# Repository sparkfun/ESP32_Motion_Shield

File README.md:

SparkFun <PRODUCT NAME>
========================================

The [ESP32 Thing Motion Shield](https://www.sparkfun.com/products/14430) is a versatile addition to our [ESP32 Thing](https://www.sparkfun.com/products/13907).  Small movements can be detected with the tried and true LSM9DS1 IMU, large movements and time can be detected with the addition of a GPS sensor.  There's a port for the [GP-20U7](https://www.sparkfun.com/products/13740) module, and breakout pins for any serial device.  Data can be easily logged by adding an microSD card to the slot.  There is also an additional user led on pin 13.

Repository Contents
-------------------

* **/Documentation** - Test plan and record.
* **/Hardware** - Eagle design files (.brd, .sch)
* **/Production** - Production panel files (.brd)
* **/Software** - Example programs for the ESP32 that can support functions of the Motion Shield.  These are used in the hookup guide.

Documentation
--------------
* **[Motion Shield Hookup Guide](https://learn.sparkfun.com/tutorials/esp32-thing-motion-shield-hookup-guide)** - Basic hookup guide for the ESP32 Motion Shield.
* **[ESP32 Hookup Guide](https://learn.sparkfun.com/tutorials/esp32-thing-hookup-guide)** - Basic hookup guide for the ESP32 Thing.

Product Versions
----------------
* [DEV-14430](https://www.sparkfun.com/products/14430) - ESP32 Motion Shield

Version History
---------------
* [V_1.0.0a](https://github.com/sparkfun/ESP32_Motion_Shield/releases/tag/v1.0.0a) - Software Update.
* [V_1.0.0](https://github.com/sparkfun/ESP32_Motion_Shield/tree/V_1.0.0) - Product release.

License Information
-------------------

This product is _**open source**_! 

Please review the LICENSE.md file for license information. 

If you have any questions or concerns on licensing, please contact techsupport@sparkfun.com.

Distributed as-is; no warranty is given.

- Your friends at SparkFun.

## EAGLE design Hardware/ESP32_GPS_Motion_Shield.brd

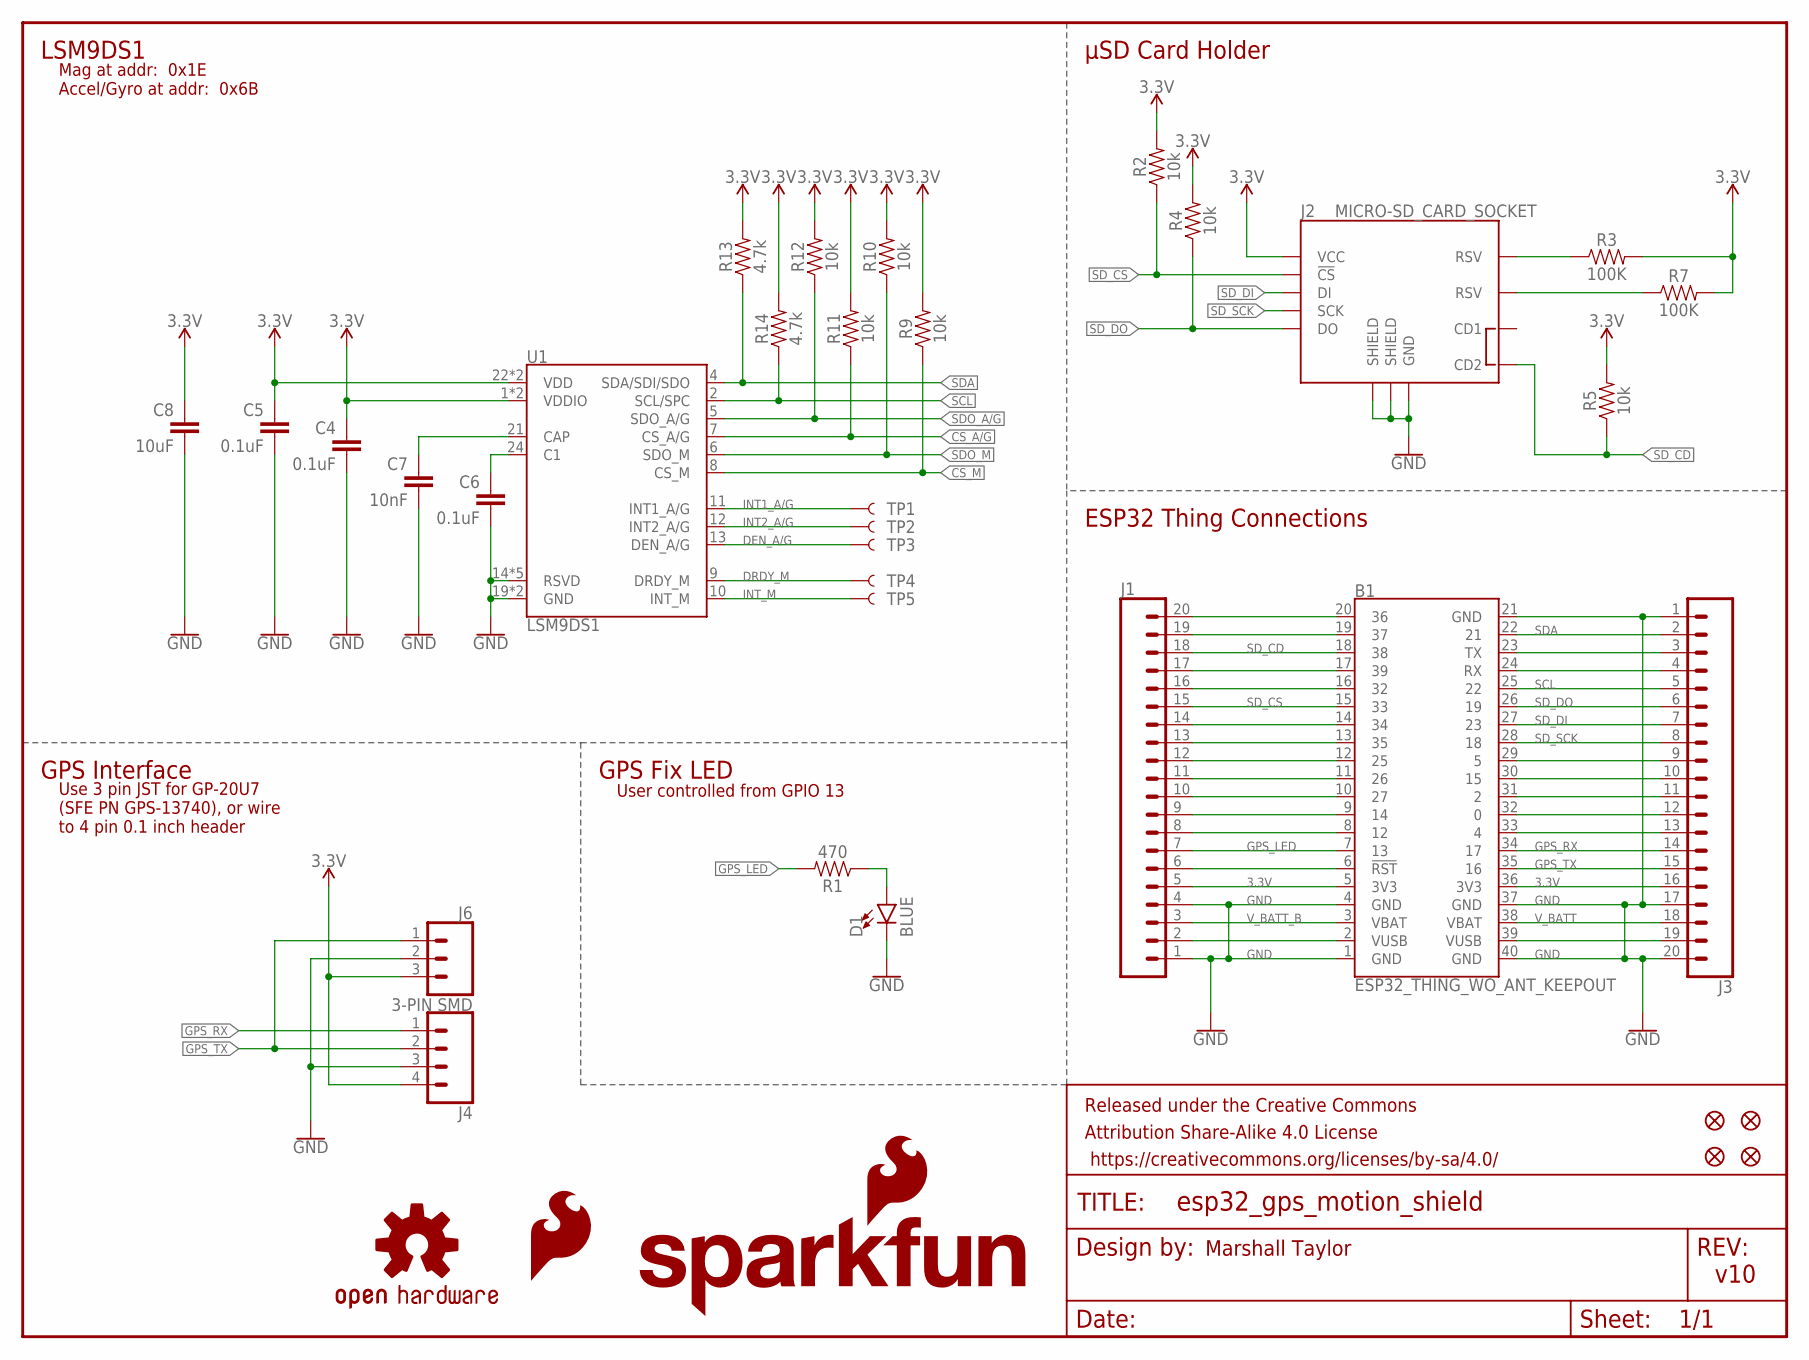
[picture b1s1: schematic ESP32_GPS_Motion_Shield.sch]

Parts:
B1: ESP32_THING_WO_ANT_KEEPOUT; ESP32_THING_NO_ANT
C4, C5, C6: 0.1uF; 0402
C7: 10nF; 0603
C8: 10uF; 0603
D1: BLUE; LED-0603
FD1, FD2, FD3, FD4: FIDUCIALUFIDUCIAL; FIDUCIAL-MICRO
FRAME1: FRAME-LETTER; CREATIVE_COMMONS
J1, J3: CONN_20NOSILK; 1X20_NOSILK
J2: MICRO-SD_CARD_SOCKET; MICRO-SD-SOCKET
J4: CONN_04; 1X04
J6: 3-PIN SMD; JST-3-SMD
LOGO1: OSHW-LOGOS; OSHW-LOGO-S
LOGO2: SFE_LOGO_NAME_FLAME.2_INCH; SFE_LOGO_NAME_FLAME_.2
LOGO3: SFE_LOGO_FLAME.1_INCH; SFE_LOGO_FLAME_.1
R1: 470; 0603
R2, R4, R5, R9, R10, R11, R12: 10k; 0603
R3, R7: 100K; 0402
R13, R14: 4.7k; 0603
TP1, TP2, TP3, TP4, TP5: TEST-POINT3; PAD.03X.03
U1: LSM9DS1; LGA-24-3.5X3

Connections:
3.3V: B1.5 (3V3), B1.36 (3V3), C4.1, C5.1, C8.1, J1.5, J2.VCC, J3.16, J4.4, J6.3 (1), R2.2, R3.2, R4.2, R5.2, R7.2, R9.2, R10.2, R11.2, R12.2, R13.2, R14.2, U1.1 (VDDIO), U1.3 (VDDIO), U1.22 (VDD), U1.23 (VDD)
C1: C6.1, U1.24 (C1)
CAP: C7.1, U1.21 (CAP)
CS_A/G: R11.1, U1.7 (CS_A/G)
CS_M: R9.1, U1.8 (CS_M)
DEN_A/G: TP3.P$1, U1.13 (DEN_A/G)
DRDY_M: TP4.P$1, U1.9 (DRDY_M)
GND: B1.1 (GND), B1.4 (GND), B1.21 (GND), B1.37 (GND), B1.40 (GND), C4.2, C5.2, C6.2, C7.2, C8.2, D1.C, J1.1, J1.4, J2.GND, J2.GND1 (SHIELD), J2.GND3 (SHIELD), J3.1, J3.17, J3.20, J4.3, J6.2, U1.14 (RSVD), U1.15 (RSVD), U1.16 (RSVD), U1.17 (RSVD), U1.18 (RSVD), U1.19 (GND), U1.20 (GND)
GPS_LED: B1.7 (13), J1.7, R1.2
GPS_RX: B1.34 (17), J3.14, J4.1
GPS_TX: B1.35 (16), J3.15, J4.2, J6.1 (3)
INT1_A/G: TP1.P$1, U1.11 (INT1_A/G)
INT2_A/G: TP2.P$1, U1.12 (INT2_A/G)
INT_M: TP5.P$1, U1.10 (INT_M)
unnamed: D1.A, R1.1
unnamed: B1.30 (15), J3.10
unnamed: B1.17 (39), J1.17
unnamed: B1.16 (32), J1.16
unnamed: B1.19 (37), J1.19
unnamed: B1.10 (27), J1.10
unnamed: B1.14 (34), J1.14
unnamed: J2.RSV1 (RSV), R3.1
unnamed: J2.RSV2 (RSV), R7.1
unnamed: B1.6 (!RST!), J1.6
unnamed: B1.8 (12), J1.8
unnamed: B1.9 (14), J1.9
unnamed: B1.11 (26), J1.11
unnamed: B1.12 (25), J1.12
unnamed: B1.13 (35), J1.13
unnamed: B1.20 (36), J1.20
unnamed: B1.23 (TX), J3.3
unnamed: B1.24 (RX), J3.4
unnamed: B1.29 (5), J3.9
unnamed: B1.31 (2), J3.11
unnamed: B1.32 (0), J3.12
unnamed: B1.33 (4), J3.13
SCL: B1.25 (22), J3.5, R14.1, U1.2 (SCL/SPC)
SDA: B1.22 (21), J3.2, R13.1, U1.4 (SDA/SDI/SDO)
SDO_A/G: R12.1, U1.5 (SDO_A/G)
SDO_M: R10.1, U1.6 (SDO_M)
SD_CD: B1.18 (38), J1.18, J2.CD2, R5.1
SD_CS: B1.15 (33), J1.15, J2.CS (!CS), R2.1
SD_DI: B1.27 (23), J2.DI, J3.7
SD_DO: B1.26 (19), J2.DO, J3.6, R4.1
SD_SCK: B1.28 (18), J2.SCLK (SCK), J3.8
VUSB: B1.39 (VUSB), J3.19
VUSB_B: B1.2 (VUSB), J1.2
V_BATT: B1.38 (VBAT), J3.18
V_BATT_B: B1.3 (VBAT), J1.3

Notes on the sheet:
GPS Interface
μSD Card Holder
GPS Fix LED
v10
Marshall Taylor
LSM9DS1
ESP32 Thing Connections
User controlled from GPIO 13
Use 3 pin JST for GP-20U7 (SFE PN GPS-13740), or wire to 4 pin 0.1 inch header
Mag at addr: 0x1E Accel/Gyro at addr: 0x6B

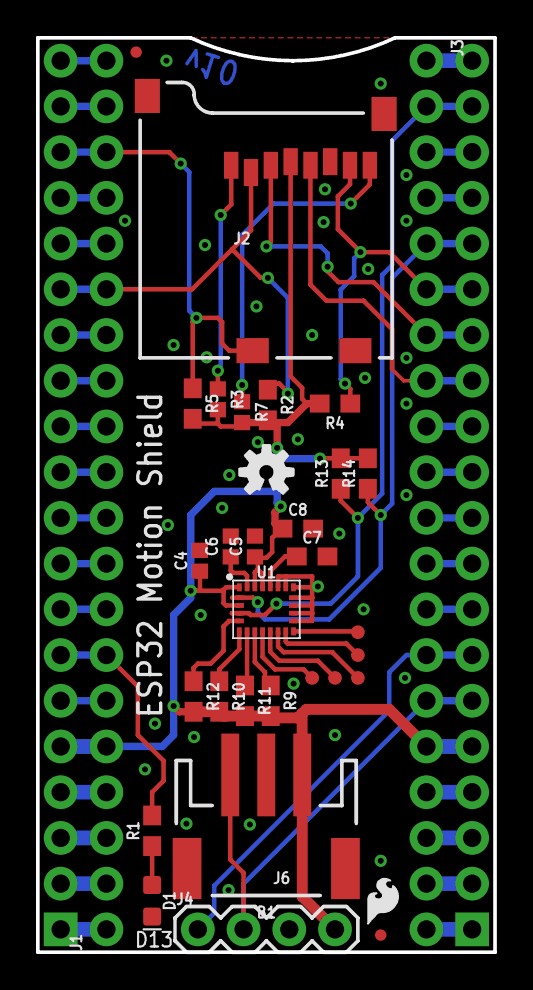
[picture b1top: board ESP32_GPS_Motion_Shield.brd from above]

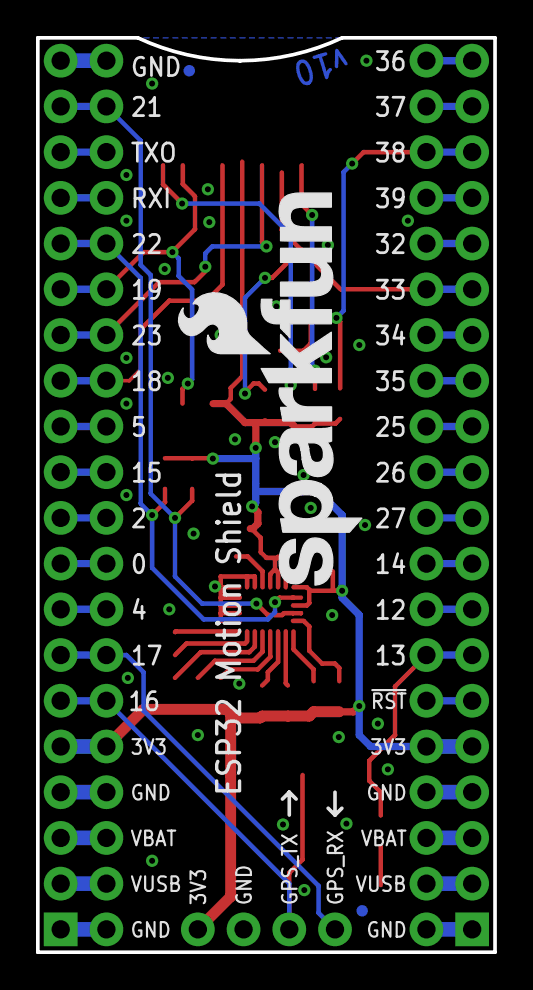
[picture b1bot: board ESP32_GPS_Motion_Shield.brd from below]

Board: 2 copper layers, 25.4 x 50.8 mm, 38 parts (3 on the bottom side), 49 nets.

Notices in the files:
parts and their libraries:
SparkFun-Connectors: Licensing: Creative Commons ShareAlike 4.0 International - https://creativecommons.org/licenses/by-sa/4.0
SparkFun-Aesthetics: Released under the Creative Commons Attribution Share-Alike 4.0 License
SparkFun-Aesthetics: https://creativecommons.org/licenses/by-sa/4.0
